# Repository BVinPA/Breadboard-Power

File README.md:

# Breadboard-Power
PCB project to connect bench power to breadboard projects

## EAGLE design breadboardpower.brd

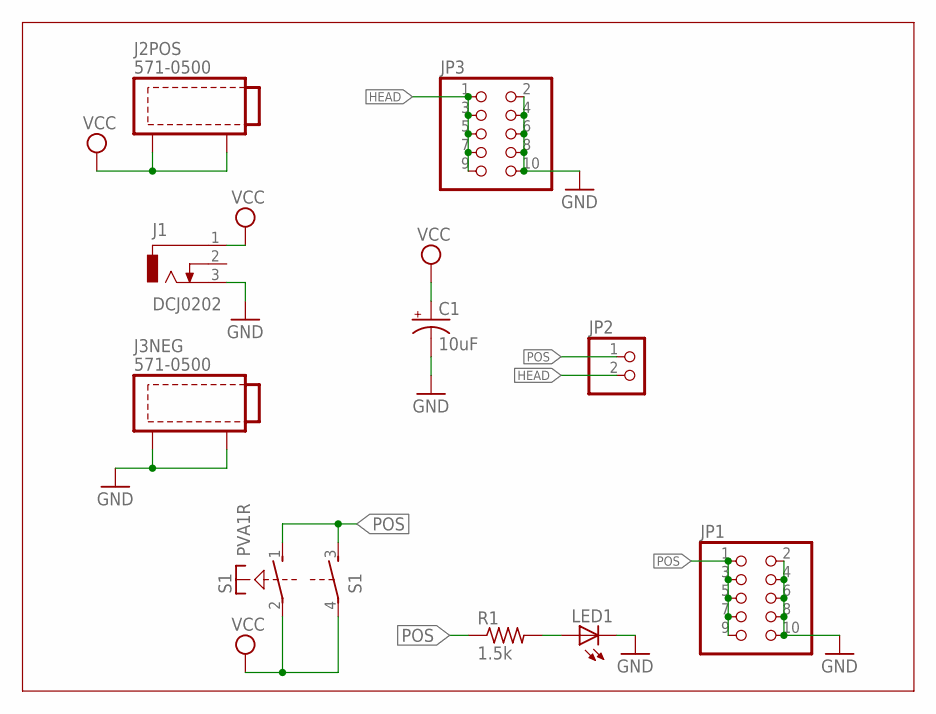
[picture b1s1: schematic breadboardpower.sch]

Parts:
C1: 10uF; E2,5-5
J1: DCJ0202
J2POS, J3NEG: 571-0500
JP1, JP3: PINHD-2X5; 2X05
JP2: PINHD-1X2; 1X02
LED1: LED3MM
R1: 1.5k; 0207/10
S1: PVA1R

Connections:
GND: C1.-, J1.3, J3NEG.1, J3NEG.2, JP1.2, JP1.4, JP1.6, JP1.8, JP1.10, JP3.2, JP3.4, JP3.6, JP3.8, JP3.10, LED1.K (C)
HEAD: JP2.2, JP3.1, JP3.3, JP3.5, JP3.7, JP3.9
unnamed: LED1.A, R1.2
POS: JP1.1, JP1.3, JP1.5, JP1.7, JP1.9, JP2.1, R1.1, S1.1 (S), S1.3 (S)
VCC: C1.+, J1.1, J2POS.1, J2POS.2, S1.2, S1.4

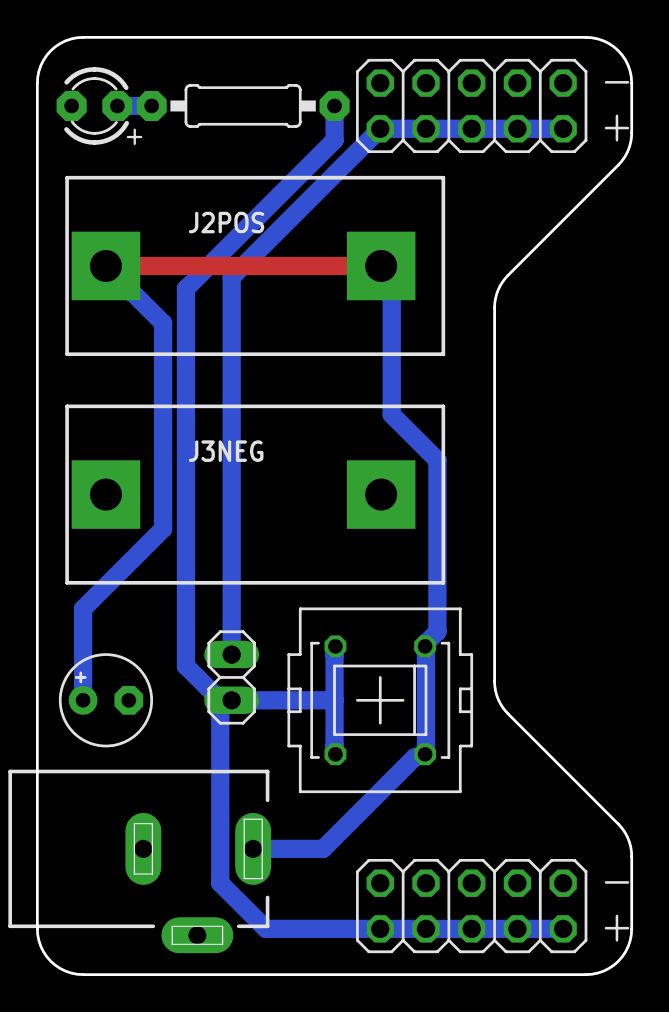
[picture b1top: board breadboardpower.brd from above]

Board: 2 copper layers, 33.0 x 52.1 mm, 11 parts (1 on the bottom side), 5 nets.

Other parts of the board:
U$1: OSHW_5MM

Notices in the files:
parts and their libraries:
con-deltron: Copyright (C) 2011, Bob Starr
